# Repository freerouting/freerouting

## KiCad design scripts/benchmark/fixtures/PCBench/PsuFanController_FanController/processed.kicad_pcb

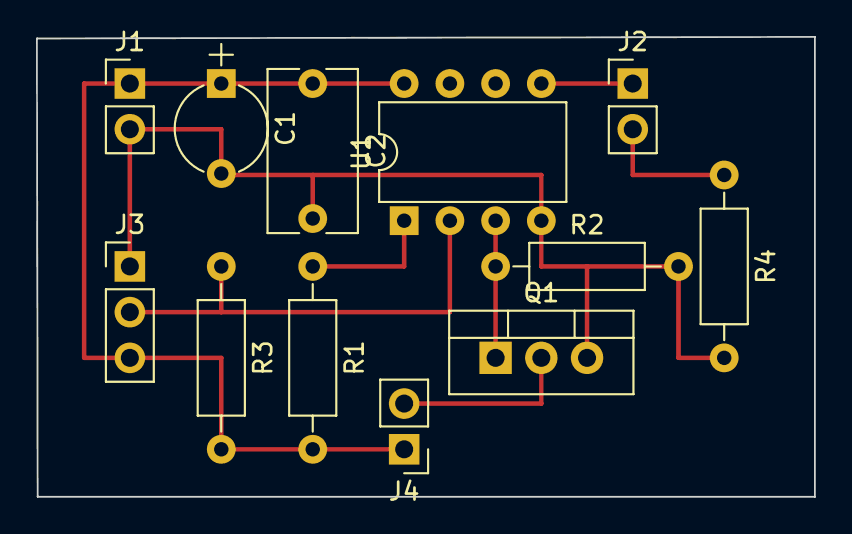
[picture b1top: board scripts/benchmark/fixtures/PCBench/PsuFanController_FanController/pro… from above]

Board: 2 copper layers, 43.2 x 25.5 mm, 12 parts (0 on the bottom side), 8 nets.

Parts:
C1: 1uF; CP_Radial_Tantal_D5.0mm_P5.00mm
C2: 0.1uF; C_Rect_L9.0mm_W4.9mm_P7.50mm_MKT
J1: PWR; Pin_Header_Straight_1x02_Pitch2.54mm
J2: LED; Pin_Header_Straight_1x02_Pitch2.54mm
J3: DS18B20; Pin_Header_Straight_1x03_Pitch2.54mm
J4: Fan; Pin_Header_Straight_1x02_Pitch2.54mm
Q1: IRL3103PBF; TO-220_Vertical
R1, R2: 10K; R_Axial_DIN0207_L6.3mm_D2.5mm_P10.16mm_Horizontal
R3: 4K7; R_Axial_DIN0207_L6.3mm_D2.5mm_P10.16mm_Horizontal
R4: 270; R_Axial_DIN0207_L6.3mm_D2.5mm_P10.16mm_Horizontal
U1: ATTINY85-20PU; DIP-8_W7.62mm

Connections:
/VCC: C1.1, C2.1, J1.1, J3.3, J4.1, R1.2, R3.2, U1.8
GND: C1.2, C2.2, J1.2, J3.1, Q1.3, R2.2, R4.2, U1.4
unnamed: J2.1, U1.5
unnamed: J2.2, R4.1
unnamed: J3.2, R3.1, U1.2
unnamed: J4.2, Q1.2
unnamed: Q1.1, R2.1, U1.3
unnamed: R1.1, U1.1

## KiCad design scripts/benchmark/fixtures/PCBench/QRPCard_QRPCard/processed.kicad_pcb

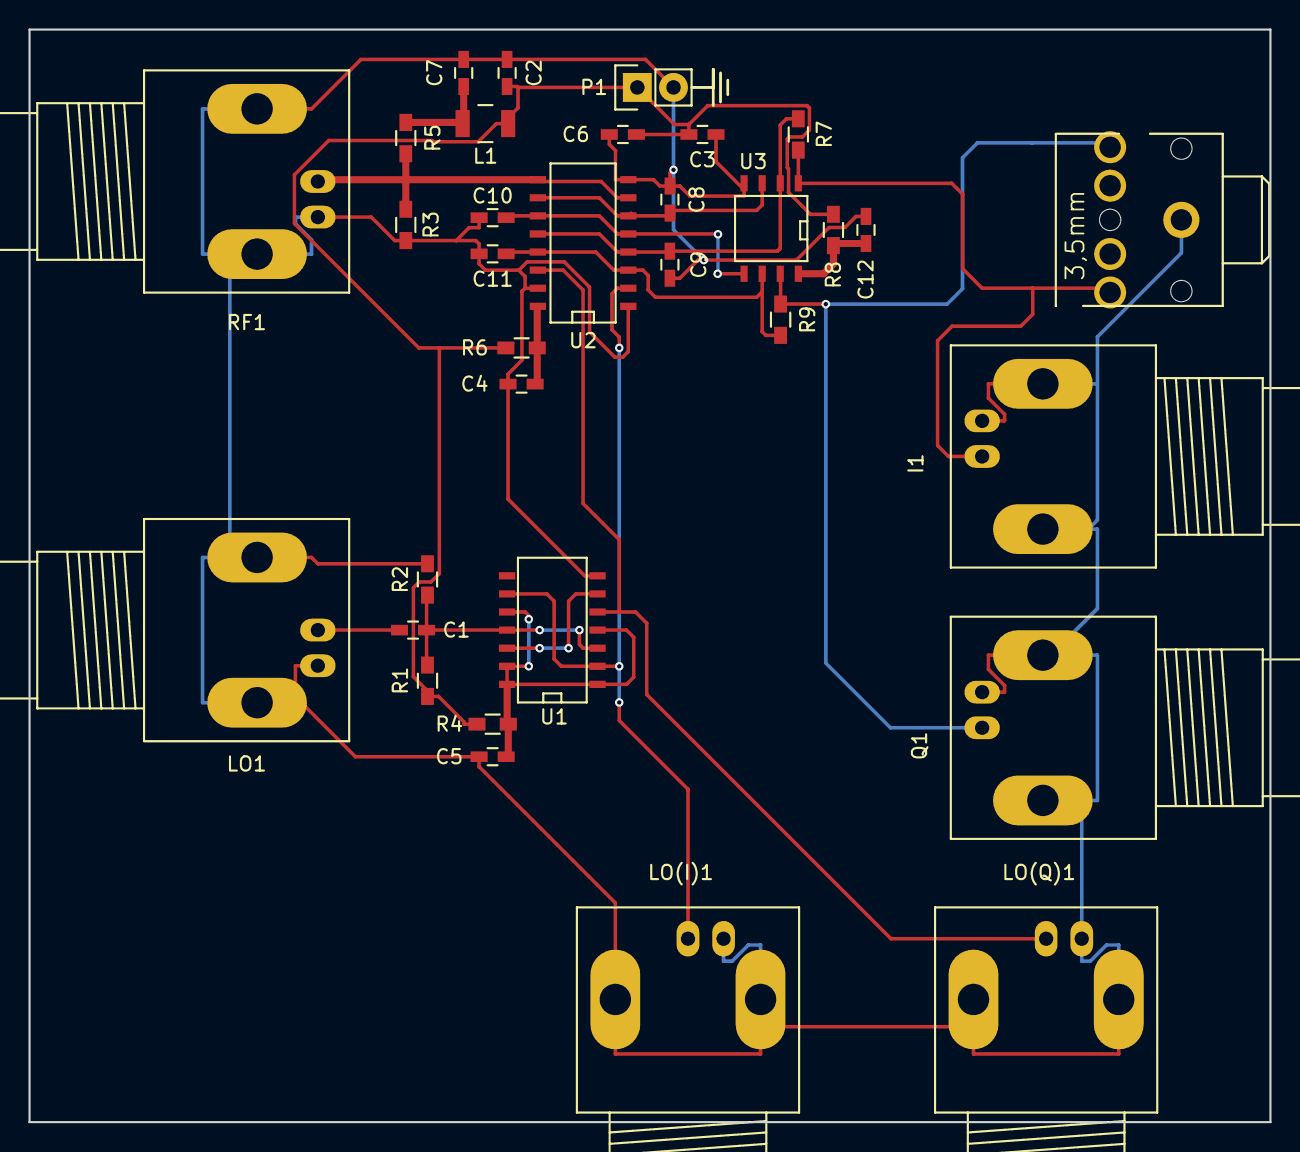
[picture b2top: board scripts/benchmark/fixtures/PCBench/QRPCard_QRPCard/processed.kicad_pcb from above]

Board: 2 copper layers, 87.1 x 76.7 mm, 33 parts (0 on the bottom side), 18 nets.

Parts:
C1, C4, C5, C8, C9, C10, C11, C12: 0.1uF; C_0603_HandSoldering
C2, C3, C7: 0.01uF; C_0603_HandSoldering
C6: 10uF; C_0603_HandSoldering
I1: BNC; BNC_Socket_TYCO-AMP_LargePads
J1: STX-3100-5N; STX3100
L1: 470uH; Neosid_Inductor_SM-NE30_SMD1210
LO1: BNC; BNC_Socket_TYCO-AMP_LargePads
LO(I)1: BNC; BNC_Socket_TYCO-AMP_LargePads
LO(Q)1: BNC; BNC_Socket_TYCO-AMP_LargePads
P1: +5v; Pin_Header_Straight_1x02
Q1: BNC; BNC_Socket_TYCO-AMP_LargePads
R1: 560k; R_0603_HandSoldering
R2: 220k; R_0603_HandSoldering
R3, R4, R5, R6, R8: 100; R_0603_HandSoldering
R7, R9: 100k; R_0603_HandSoldering
RF1: BNC; BNC_Socket_TYCO-AMP_LargePads
U1: SN74HC74; SOIC-14_N
U2: FST3253; SO-16-N
U3: TSV992A; SOIC-8-N

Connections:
+5V: C2.2, C3.2, C6.2, L1.1, P1.1, R1.1, R4.1, R6.1, R8.1
GND: C2.1, C3.1, C4.1, C5.2, C6.1, C7.1, C8.1, C9.1, C10.1, C11.1, C12.1, I1.2, J1.1, LO1.2, LO(I)1.2, LO(Q)1.2, P1.2, Q1.2, R2.2, R3.1, RF1.2, U1.7, U2.1, U2.8, U2.15, U3.4
unnamed: C1.1, R1.2, R2.1, U1.3, U1.11
unnamed: C1.2, LO1.1
unnamed: C4.2, R6.2, U2.16
unnamed: C5.1, R4.2, U1.1, U1.4, U1.10, U1.13, U1.14
unnamed: C7.2, L1.2, R5.1
unnamed: C8.2, U2.6, U2.10, U3.3
unnamed: C9.2, R7.2, U2.4, U2.12, U3.2
unnamed: C10.2, U2.5, U2.11, U3.5
unnamed: C11.2, R9.2, U2.3, U2.13, U3.6
unnamed: C12.2, R8.2, U3.8
unnamed: I1.1, J1.2, R7.1, U3.1
unnamed: J1.5, Q1.1, R9.1, U3.7
unnamed: LO(I)1.1, U1.2, U1.9, U2.2
unnamed: LO(Q)1.1, U1.5, U2.14
unnamed: R3.2, R5.2, RF1.1, U2.7, U2.9
unnamed: U1.6, U1.12

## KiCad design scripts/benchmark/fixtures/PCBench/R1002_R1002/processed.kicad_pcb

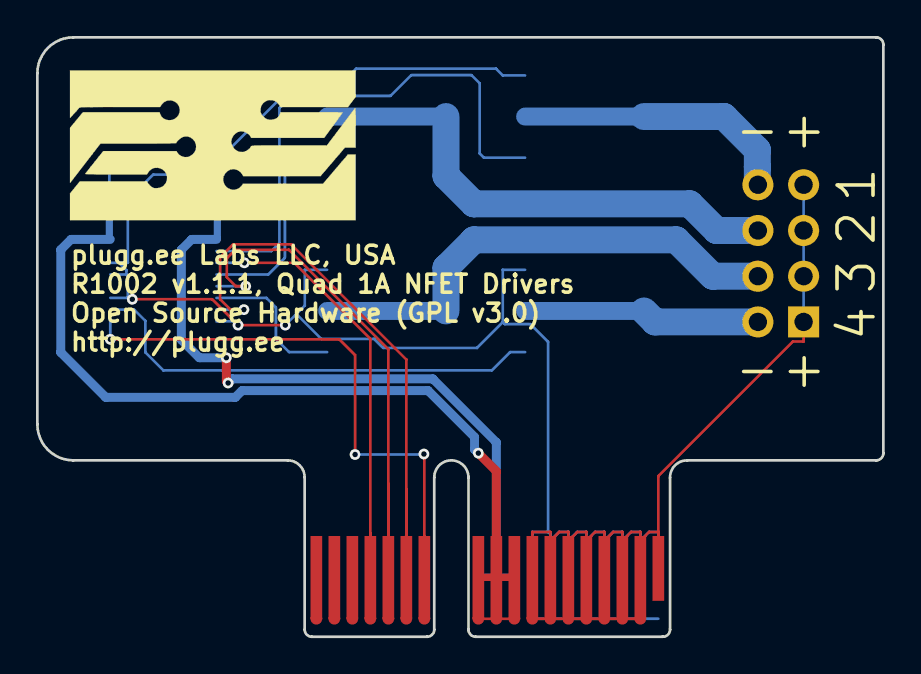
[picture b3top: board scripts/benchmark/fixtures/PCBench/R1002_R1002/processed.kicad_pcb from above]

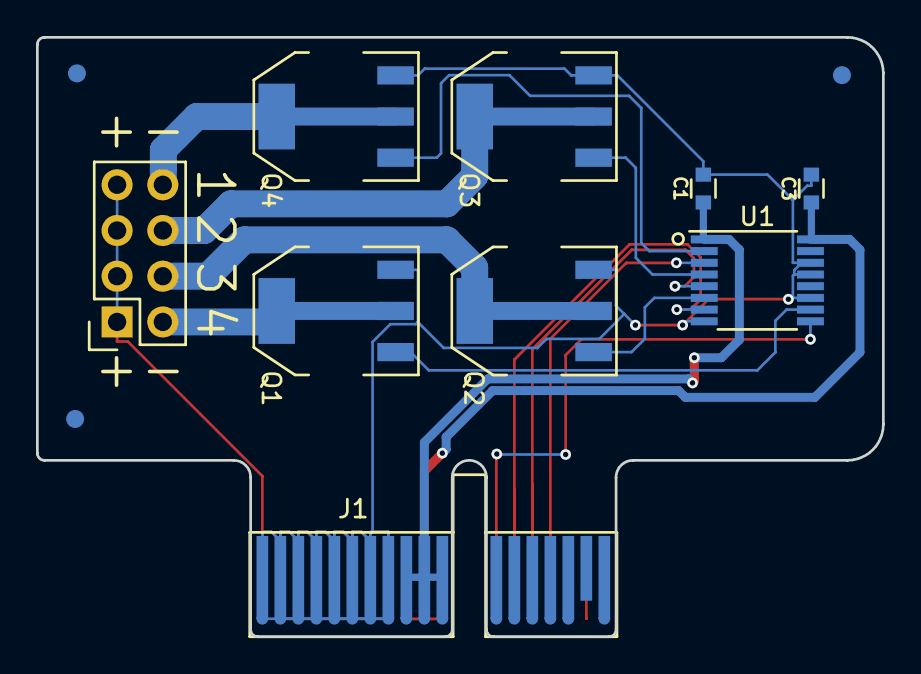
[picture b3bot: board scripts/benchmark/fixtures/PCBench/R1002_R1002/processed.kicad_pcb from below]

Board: 2 copper layers, 47.0 x 33.3 mm, 13 parts (12 on the bottom side), 16 nets.

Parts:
A1: ART; pluggeeLabsIcon-16X8
C1, C3: CC0603KRX7R9BB104; CAPC0603
FID1, FID2, FID3: FIDTOP001
J1: PCIEXPRESS-X1
J2: CONN254P-02X04
Q1, Q2, Q3, Q4: Q_NMOS_GDSD; SOT-223
U1: MC14504B-TSSOP; SOP65P500X440X120-16

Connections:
+3V3: C1.1, J1.B9, J1.B10, J1.B11, U1.1
+5V: C3.1, J1.A9, J1.A10, J1.A11, U1.16
/DN1: J2.8, Q4.2, Q4.4
/DN2: J2.6, Q3.2, Q3.4
/DN3: J2.4, Q2.2, Q2.4
/DN4: J2.2, Q1.2, Q1.4
/GN1: Q4.1, U1.2
/GN2: Q3.1, U1.4
/GN3: Q2.1, U1.6
/GN4: Q1.1, U1.10
GND: C1.2, C3.2, J1.B1, J1.B2, J1.B3, J1.B4, J1.B5, J1.B6, J1.B7, J1.B8, Q1.3, Q2.3, Q3.3, Q4.3, U1.8, U1.11, U1.13, U1.14
HT: J1.A1, J1.A2, J1.A3, J1.A4, J1.A5, J1.A6, J1.A7, J1.A8, J2.1, J2.3, J2.5, J2.7
PX1: J1.A12, U1.9
PX2: J1.A13, U1.7
PX3: J1.A14, U1.5
PX4: J1.A15, U1.3

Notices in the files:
scripts/benchmark/fixtures/PCBench/R1002_R1002/processed.kicad_pcb:
Open Source Hardware (GPL v3.0)
